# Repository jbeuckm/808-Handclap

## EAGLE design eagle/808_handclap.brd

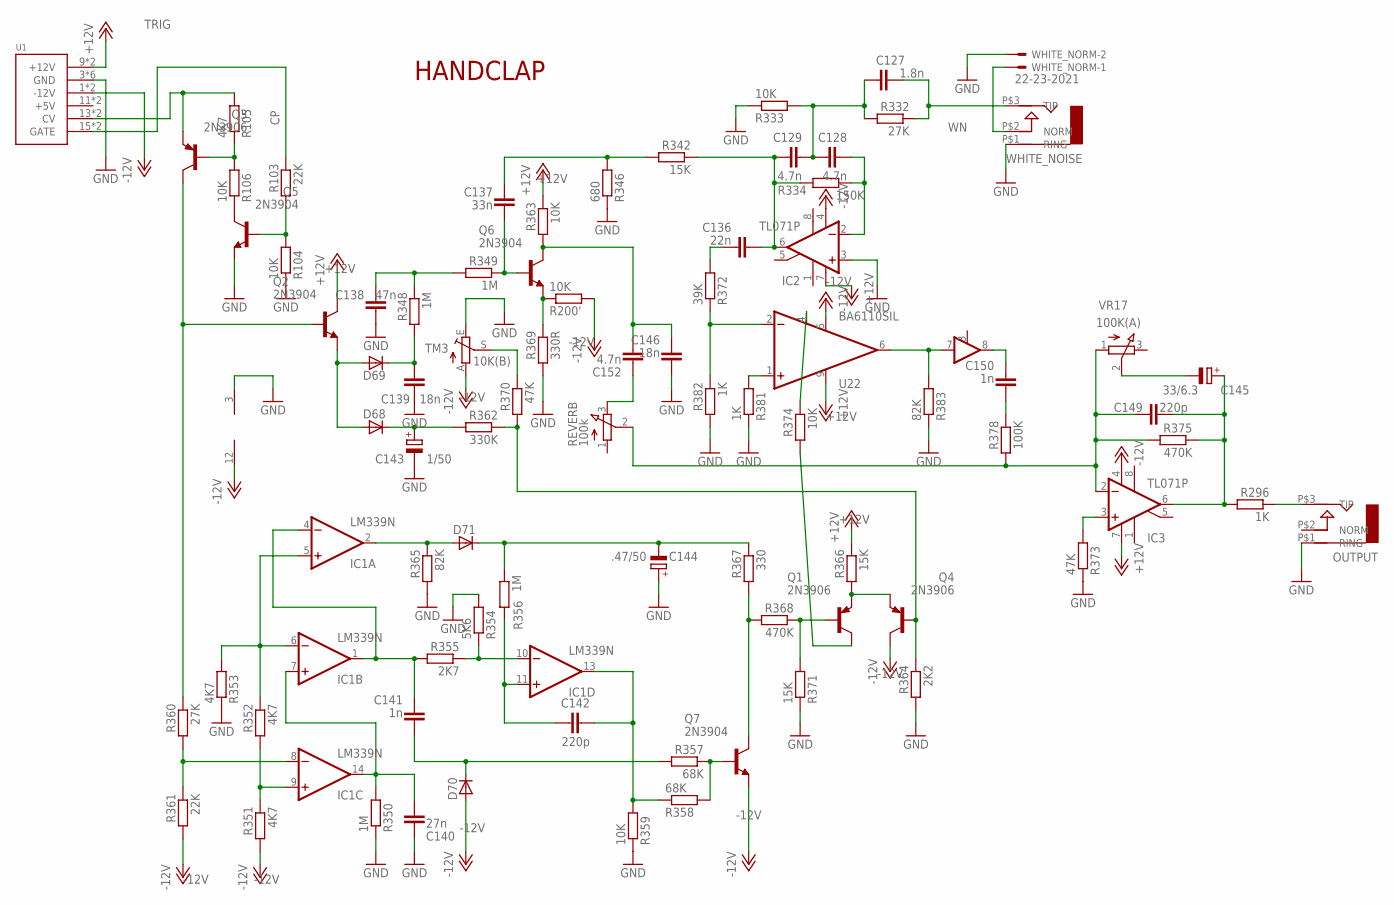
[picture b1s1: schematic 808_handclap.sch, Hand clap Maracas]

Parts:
C127: 1.8n; C075-032X103
C128, C129, C152: 4.7n; C035-025X75
C136: 22n; C050-024X044
C137: 33n; C075-032X103
C138: 47n; C050-024X044
C139: 18n; C035-025X75
C140: 27n; C050-024X044
C141, C150: 1n; C035-025X75
C142: 220p; C050-025X075
C143: 1/50; E2-5
C144: .47/50; E2-5
C145: 33/6.3; E3,5-8
C146: 18n; C035-030X60
C149: 220p; C050-024X044
D68, D70: 1N4148DO35-7; DO35-7
D69, D71: 1N4148DO35-10; DO35-10
IC1: LM339N; DIL14
IC2, IC3: TL071P; DIL08
OUTPUT: AUDIO-JACK; ERTHENVAR-JACK-90DEG
Q1, Q3, Q4: 2N3906; TO92
Q2, Q5, Q6, Q7: 2N3904; TO92
R103: 22K; 0207/7
R104, R200', R359, R363, R374: 10K; 0207/7
R105, R351: 4K7; 0207/5V
R106, R333: 10K; 0207/5V
R296: 1K; 0207/7
R332, R360: 27K; 0207/7
R334: 150K; 0207/7
R342, R366, R371: 15K; 0207/7
R346: 680; 0207/7
R348, R350, R356: 1M; 0207/7
R349: 1M; 0207/5V
R352: 4K7; 0309/10
R353: 4K7; 0207/7
R354: 5K6; 0207/5V
R355: 2K7; 0207/5V
R357: 68K; 0207/7
R358: 68K; 0207/5V
R361: 22K; 0207/2V
R362: 330K; 0309/10
R364: 2K2; 0309/10
R365: 82K; 0207/5V
R367: 330; 0207/7
R368: 470K; 0207/7
R369: 330R; 0207/7
R370: 47K; 0309/10
R372: 39K; 0207/7
R373: 47K; 0207/7
R375: 470K; 0207/5V
R378: 100K; 0207/7
R381, R382: 1K; 0207/5V
R383: 82K; 0207/7
REVERB: 100k; 3RP/1610N
TM3: 10K(B); S64YW
U1: POWER; POWER_16
U22: BA6110SIL; SIL09
VR17: 100K(A); 3RP/1610N
WHITE_NOISE: AUDIO-JACK; ERTHENVAR-JACK-90DEG
WHITE_NORM: 22-23-2021

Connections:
+12V: IC2.7 (V+), IC3.7 (V+), Q2.1 (C), R363.1, R366.1, U1.9 (+12V), U1.10 (+12V), U22.9 (V+)
-12V: D70.A, IC1.12 (GND), IC2.4 (V-), IC3.4 (V-), Q4.1 (C), Q7.3 (E), R200'.2, R351.2, R361.2, TM3.A, U1.1 (-12V), U1.2 (-12V), U22.5 (V-)
CP: R103.1, U1.15 (GATE), U1.16 (GATE)
GND: C138.2, C139.P$1 (1), C140.1, C143.-, C144.+, C146.P$2 (2), IC1.3 (V+), IC2.3 (+IN), OUTPUT.P$1 (RING), Q5.3 (E), R104.1, R333.1, R346.1, R350.1, R353.1, R354.2, R359.1, R364.2, R365.2, R369.2, R371.1, R373.1, R381.1, R382.2, R383.1, TM3.E, U1.3 (GND), U1.4 (GND), U1.5 (GND), U1.6 (GND), U1.7 (GND), U1.8 (GND), WHITE_NOISE.P$1 (RING), WHITE_NORM.2
unnamed: OUTPUT.P$3 (TIP), R296.1
unnamed: WHITE_NOISE.P$2 (NORM), WHITE_NORM.1
unnamed: Q5.1 (C), R106.1
unnamed: Q5.2 (B), R103.2, R104.2
unnamed: C129.P$2 (2), C136.1, IC2.6 (OUT), R334.2, R342.1
unnamed: Q3.2 (B), R105.1, R106.2
unnamed: C137.2, Q6.2 (B), R349.1
unnamed: C139.P$2 (2), D69.C, R348.2
unnamed: Q6.3 (E), R200'.1, R369.1
unnamed: Q2.2 (B), Q3.1 (C), R360.1
unnamed: D68.A, D69.A, Q2.3 (E)
unnamed: C138.1, R348.1, R349.2
unnamed: C146.P$1 (1), C152.P$1 (1), Q6.1 (C), R363.2
unnamed: C143.+, D68.C, R362.2
unnamed: Q4.2 (B), R362.1, R364.1, R370.2
unnamed: R370.1, TM3.S
unnamed: C137.1, R342.2, R346.2
unnamed: D71.A, IC1.2 (OUT), R365.1
unnamed: C127.2, C128.P$2 (2), C129.P$1 (1), R332.2, R333.2
unnamed: C128.P$1 (1), IC2.2 (-IN), R334.1
unnamed: C136.2, R372.2
unnamed: R372.1, R382.1, U22.2 (-IN)
unnamed: C152.P$2 (2), REVERB.3 (E)
unnamed: R381.2, U22.1 (+IN)
unnamed: R374.1, U22.4 (C)
unnamed: R383.2, U22.6 (OUT), U22.7 (IN1)
unnamed: C150.P$2 (2), R378.1
unnamed: C150.P$1 (1), U22.8 (OUT1)
unnamed: IC1.5 (+IN), IC1.6 (-IN), R352.1, R353.2
unnamed: C144.-, D71.C, R356.1, R367.1
unnamed: Q1.2 (B), R368.1, R371.2
unnamed: Q1.3 (E), Q4.3 (E), R366.2
unnamed: C141.P$1 (1), IC1.1 (OUT), IC1.4 (-IN), R355.2
unnamed: Q1.1 (C), R374.2
unnamed: Q7.1 (C), R367.2, R368.2
unnamed: IC1.9 (+IN), R351.1, R352.2
unnamed: C142.2, IC1.11 (+IN), R356.2
unnamed: IC1.10 (-IN), R354.1, R355.1
unnamed: IC1.8 (-IN), R360.2, R361.1
unnamed: Q7.2 (B), R357.1, R358.2
unnamed: C141.P$2 (2), D70.C, R357.2
unnamed: C140.2, IC1.7 (+IN), IC1.14 (OUT), R350.2
unnamed: C142.1, IC1.13 (OUT), R358.1, R359.2
unnamed: IC3.3 (+IN), R373.2
unnamed: C149.2, IC3.2 (-IN), R375.2, R378.2, REVERB.2 (S), VR17.1 (A)
unnamed: C145.-, VR17.2 (S)
unnamed: C145.+, C149.1, IC3.6 (OUT), R296.2, R375.1
TRIG: Q3.3 (E), R105.2, U1.13 (CV), U1.14 (CV)
WN: C127.1, R332.1, WHITE_NOISE.P$3 (TIP)

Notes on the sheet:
HANDCLAP

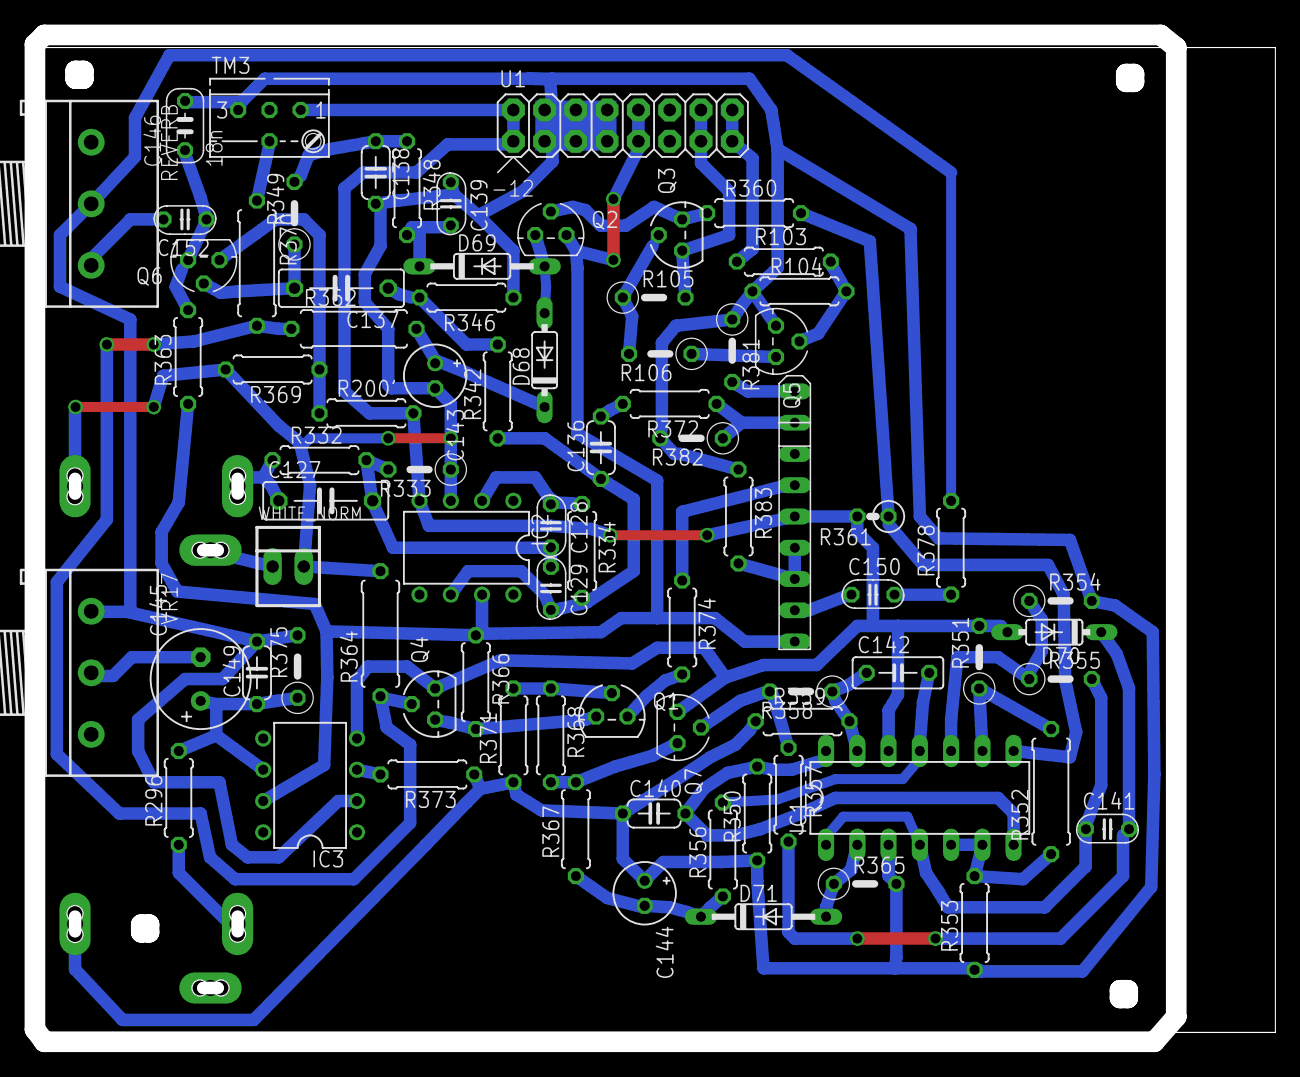
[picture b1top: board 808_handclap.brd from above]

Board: 2 copper layers, 100.8 x 81.8 mm, 82 parts (0 on the bottom side), 53 nets.

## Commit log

2016-01-23 2n3904 and 2n3906
2016-01-23 gcode for converted version
2016-04-25 starting over from yocto
2016-04-25 lm339
2016-04-25 opamps
2016-04-25 pretty up schemo
2016-04-25 variable reverb mod
2016-04-26 88pct autorouted
2016-04-26 manual mode
2016-04-27 more hand routes
2016-04-27 routed
2016-04-27 tweaks
2016-04-27 cutout
2016-04-28 changed c140 to 27n to make separate hits audible
